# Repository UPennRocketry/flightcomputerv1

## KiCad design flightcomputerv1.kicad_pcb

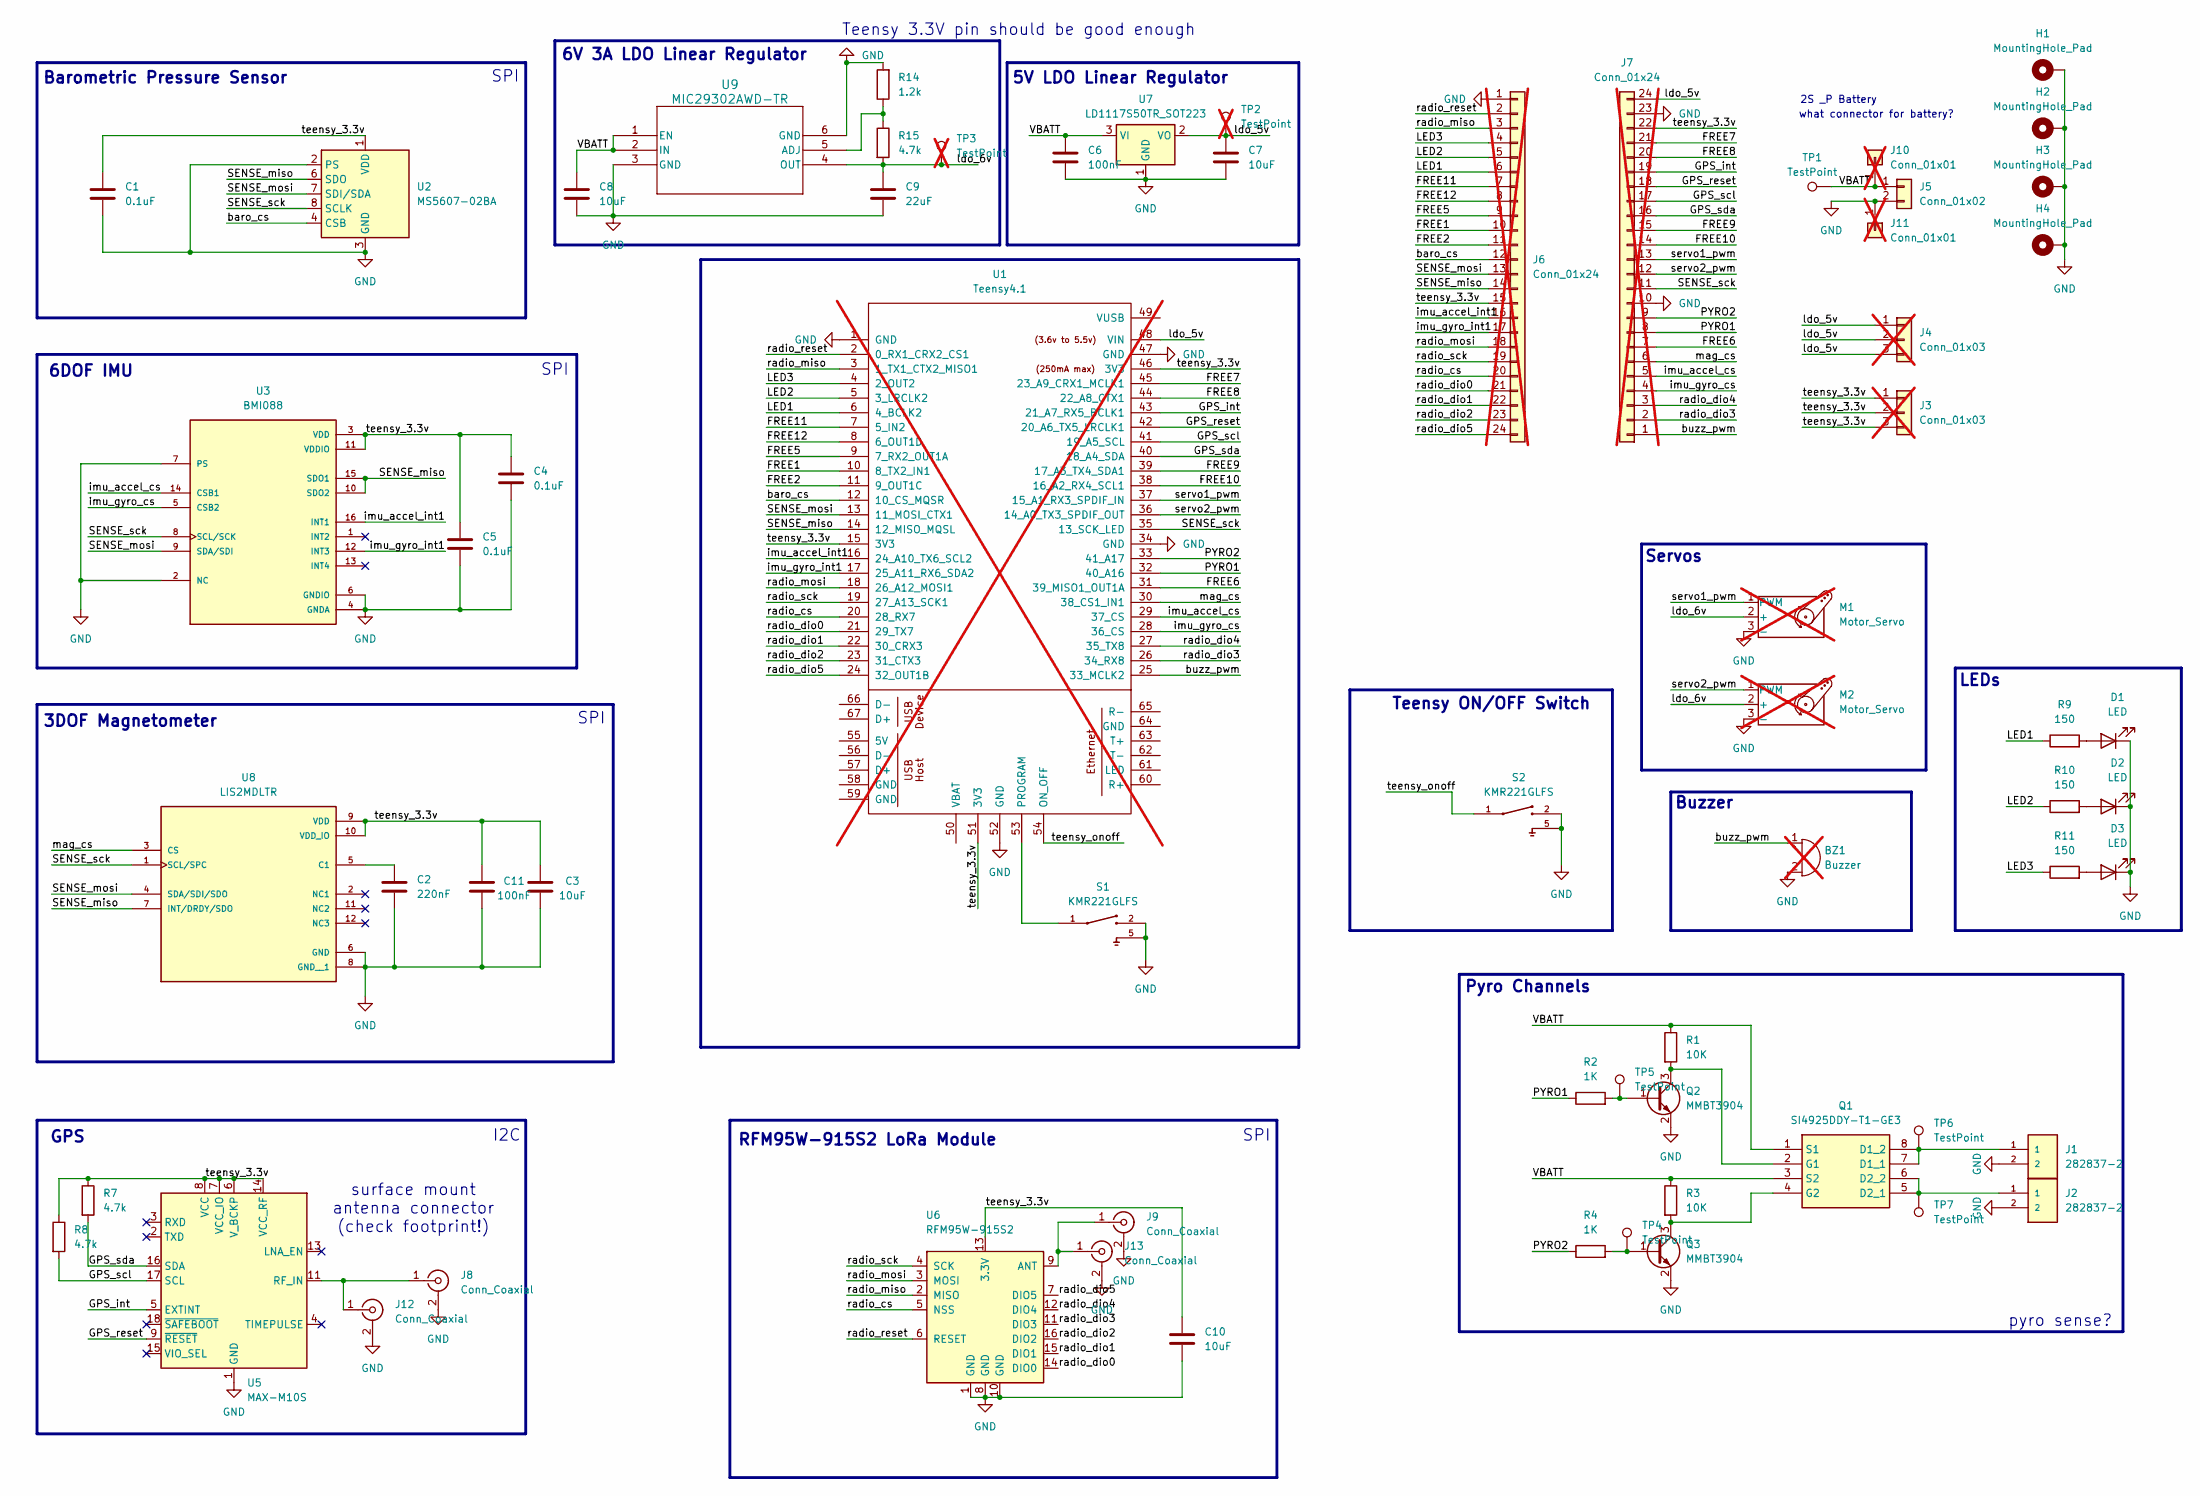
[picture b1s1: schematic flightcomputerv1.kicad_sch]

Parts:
BZ1: Buzzer; MagneticBuzzer_PUI_AT-0927-TT-6-R; MPN AT-0927-TT-6-R; not fitted
C1, C4, C5: 0.1uF; C_0402_1005Metric_Pad0.74x0.62mm_HandSolder
C2: 220nF; C_0402_1005Metric_Pad0.74x0.62mm_HandSolder
C3: 10uF; C_0402_1005Metric_Pad0.74x0.62mm_HandSolder
C6: 100nF; C_0603_1608Metric_Pad1.08x0.95mm_HandSolder
C7, C8, C10: 10uF; C_0603_1608Metric_Pad1.08x0.95mm_HandSolder
C9: 22uF; C_0603_1608Metric_Pad1.08x0.95mm_HandSolder
C11: 100nF; C_0402_1005Metric_Pad0.74x0.62mm_HandSolder
D1, D2, D3: LED; LED_0603_1608Metric_Pad1.05x0.95mm_HandSolder
H1, H2, H3, H4: MountingHole_Pad; MountingHole_2.2mm_M2_DIN965_Pad
J1, J2: 282837-2; TE_282837-2; PARTREV G3
J3, J4: Conn_01x03; PinHeader_1x03_P2.54mm_Vertical; not fitted
J5: Conn_01x02; JST_PH_S2B-PH-K_1x02_P2.00mm_Horizontal
J6, J7: Conn_01x24; Molex_SL_171971-0024_1x24_P2.54mm_Vertical; not fitted
J8, J9: Conn_Coaxial; SMA_Amphenol_132134-10_Vertical; MPN 132134
J10, J11: Conn_01x01; PinHeader_1x01_P2.54mm_Vertical; not fitted
J12, J13: Conn_Coaxial; U.FL_Hirose_U.FL-R-SMT-1_Vertical
M1, M2: Motor_Servo; PinHeader_1x03_P2.54mm_Vertical; not fitted
Q1: SI4925DDY-T1-GE3; SOIC127P600X175-8N; MPN SI4925DDY-T1-GE3
Q2: MMBT3904; SOT-23; MPN MMBT3904LT3G
Q3: MMBT3904; SOT-23
R1, R3: 10K; R_0603_1608Metric_Pad0.98x0.95mm_HandSolder
R2, R4: 1K; R_0603_1608Metric_Pad0.98x0.95mm_HandSolder
R7, R8, R15: 4.7k; R_0603_1608Metric_Pad0.98x0.95mm_HandSolder
R9, R10, R11: 150; R_0603_1608Metric_Pad0.98x0.95mm_HandSolder
R14: 1.2k; R_0603_1608Metric_Pad0.98x0.95mm_HandSolder
S1, S2: KMR221GLFS; SW_KMR221GLFS
TP1, TP4, TP5, TP6, TP7: TestPoint; TestPoint_Pad_1.0x1.0mm
TP2, TP3: TestPoint; PinHeader_1x01_P2.54mm_Vertical; not fitted
U1: Teensy4.1; Teensy41; not fitted
U2: MS5607-02BA; LGA-8_3x5mm_P1.25mm; MPN MS560702BA03-50
U3: BMI088; PQFN50P450X300X100-16N; MPN BMI088
U5: MAX-M10S; ublox_MAX; MPN MAX-M10S-00B
U6: RFM95W-915S2; HOPERF_RFM9XW_SMD; MPN RFM95W-915S2
U7: LD1117S50TR_SOT223; SOT-223-3_TabPin2; MPN LD1117S50TR
U8: LIS2MDLTR; PQFN50P200X200X70-12N; PARTREV Rev 5
U9: MIC29302AWD-TR; TO-252-5_MCH

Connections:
/FREE1: J6.10, U1.10 (8_TX2_IN1)
/FREE2: J6.11, U1.11 (9_OUT1C)
/FREE5: J6.9, U1.9 (7_RX2_OUT1A)
/FREE6: J7.7, U1.31 (39_MISO1_OUT1A)
/FREE7: J7.21, U1.45 (23_A9_CRX1_MCLK1)
/FREE8: J7.20, U1.44 (22_A8_CTX1)
/FREE9: J7.15, U1.39 (17_A3_TX4_SDA1)
/FREE10: J7.14, U1.38 (16_A2_RX4_SCL1)
/FREE11: J6.7, U1.7 (5_IN2)
/FREE12: J6.8, U1.8 (6_OUT1D)
/GPS_int: J7.19, U1.43 (21_A7_RX5_BCLK1), U5.5 (EXTINT)
/GPS_reset: J7.18, U1.42 (20_A6_TX5_LRCLK1), U5.9 (~RESET)
/GPS_scl: J7.17, R8.2, U1.41 (19_A5_SCL), U5.17 (SCL)
/GPS_sda: J7.16, R7.2, U1.40 (18_A4_SDA), U5.16 (SDA)
/LED1: J6.6, R9.1, U1.6 (4_BCLK2)
/LED2: J6.5, R10.1, U1.5 (3_LRCLK2)
/LED3: J6.4, R11.1, U1.4 (2_OUT2)
/PYRO1: J7.8, R2.1, U1.32 (40_A16)
/PYRO2: J7.9, R4.1, U1.33 (41_A17)
/SENSE_miso: J6.14, U1.14 (12_MISO_MQSL), U2.6 (SDO), U3.10 (SDO2), U3.15 (SDO1), U8.7 (INT/DRDY/SDO)
/SENSE_mosi: J6.13, U1.13 (11_MOSI_CTX1), U2.7 (SDI/SDA), U3.9 (SDA/SDI), U8.4 (SDA/SDI/SDO)
/SENSE_sck: J7.11, U1.35 (13_SCK_LED), U2.8 (SCLK), U3.8 (SCL/SCK), U8.1 (SCL/SPC)
/VBATT: C6.1, C8.1, J5.1, J10.1, Q1.1 (S1), Q1.3 (S2), R1.1, R3.1, TP1.1, U7.3 (VI), U9.1 (EN), U9.2 (IN)
/baro_cs: J6.12, U1.12 (10_CS_MQSR), U2.4 (CSB), U2.5 (CSB)
/buzz_pwm: BZ1.1 (+), J7.1, U1.25 (33_MCLK2)
/imu_accel_cs: J7.5, U1.29 (37_CS), U3.14 (CSB1)
/imu_accel_int1: J6.16, U1.16 (24_A10_TX6_SCL2), U3.16 (INT1)
/imu_gyro_cs: J7.4, U1.28 (36_CS), U3.5 (CSB2)
/imu_gyro_int1: J6.17, U1.17 (25_A11_RX6_SDA2), U3.12 (INT3)
/ldo_5v: C7.1, J4.1, J4.2, J4.3, J7.24, TP2.1, U1.48 (VIN), U7.2 (VO)
/ldo_6v: C9.1, M1.2 (+), M2.2 (+), R15.2, TP3.1, U9.4 (OUT)
/mag_cs: J7.6, U1.30 (38_CS1_IN1), U8.3 (CS)
/radio_cs: J6.20, U1.20 (28_RX7), U6.5 (NSS)
/radio_dio0: J6.21, U1.21 (29_TX7), U6.14 (DIO0)
/radio_dio1: J6.22, U1.22 (30_CRX3), U6.15 (DIO1)
/radio_dio2: J6.23, U1.23 (31_CTX3), U6.16 (DIO2)
/radio_dio3: J7.2, U1.26 (34_RX8), U6.11 (DIO3)
/radio_dio4: J7.3, U1.27 (35_TX8), U6.12 (DIO4)
/radio_dio5: J6.24, U1.24 (32_OUT1B), U6.7 (DIO5)
/radio_miso: J6.3, U1.3 (1_TX1_CTX2_MISO1), U6.2 (MISO)
/radio_mosi: J6.18, U1.18 (26_A12_MOSI1), U6.3 (MOSI)
/radio_reset: J6.2, U1.2 (0_RX1_CRX2_CS1), U6.6 (RESET)
/radio_sck: J6.19, U1.19 (27_A13_SCK1), U6.4 (SCK)
/servo1_pwm: J7.13, M1.1 (PWM), U1.37 (15_A1_RX3_SPDIF_IN)
/servo2_pwm: J7.12, M2.1 (PWM), U1.36 (14_A0_TX3_SPDIF_OUT)
/teensy_3.3v: C1.1, C3.1, C4.1, C5.1, C10.1, C11.1, J3.1, J3.2, J3.3, J6.15, J7.22, R7.1, R8.1, U1.15 (3V3), U1.46 (3V3), U1.51 (3V3), U2.1 (VDD), U3.3 (VDD), U3.11 (VDDIO), U5.6 (V_BCKP), U5.7 (VCC_IO), U5.8 (VCC), U5.14 (VCC_RF), U6.13 (3.3V), U8.9 (VDD), U8.10 (VDD_IO)
/teensy_onoff: S2.1, U1.54 (ON_OFF)
GND: BZ1.2 (-), C1.2, C2.2, C3.2, C4.2, C5.2, C6.2, C7.2, C8.2, C9.2, C10.2, C11.2, D1.1 (K), D2.1 (K), D3.1 (K), H1.1, H2.1, H3.1, H4.1, J1.2, J2.2, J5.2, J6.1, J7.10, J7.23, J8.2 (Ext), J9.2 (Ext), J11.1, J12.2 (Ext), J13.2 (Ext), M1.3 (-), M2.3 (-), Q2.2 (E), Q3.2 (E), R14.2, S1.2, S1.5, S2.2, S2.5, U1.1 (GND), U1.34 (GND), U1.47 (GND), U1.52 (GND), U2.2 (PS), U2.3 (GND), U3.2 (NC), U3.4 (GNDA), U3.6 (GNDIO), U3.7 (PS), U5.1 (GND), U5.10 (GND), U5.12 (GND), U6.1 (GND), U6.8 (GND), U6.10 (GND), U7.1 (GND), U8.6 (GND), U8.8 (GND__1), U9.3 (GND), U9.6 (GND)
unnamed: D1.2 (A), R9.2
unnamed: D2.2 (A), R10.2
unnamed: D3.2 (A), R11.2
unnamed: J8.1 (In), J12.1 (In), U5.11 (RF_IN)
unnamed: J9.1 (In), J13.1 (In), U6.9 (ANT)
unnamed: J1.1, Q1.7 (D1_1), Q1.8 (D1_2), TP6.1
unnamed: J2.1, Q1.5 (D2_1), Q1.6 (D2_2), TP7.1
unnamed: Q1.2 (G1), Q2.3 (C), R1.2
unnamed: Q1.4 (G2), Q3.3 (C), R3.2
unnamed: Q2.1 (B), R2.2, TP5.1
unnamed: Q3.1 (B), R4.2, TP4.1
unnamed: S1.1, U1.53 (PROGRAM)
unnamed: C2.1, U8.5 (C1)
unnamed: R14.1, R15.1, U9.5 (ADJ)

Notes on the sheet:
SPI
5V LDO Linear Regulator
LEDs
GPS
Barometric Pressure Sensor
surface mount antenna connector (check footprint!)
pyro sense?
2S _P Battery
Teensy 3.3V pin should be good enough
3DOF Magnetometer
6DOF IMU
Servos
Teensy ON/OFF Switch
Buzzer
RFM95W-915S2 LoRa Module
what connector for battery?
Pyro Channels
I2C
6V 3A LDO Linear Regulator

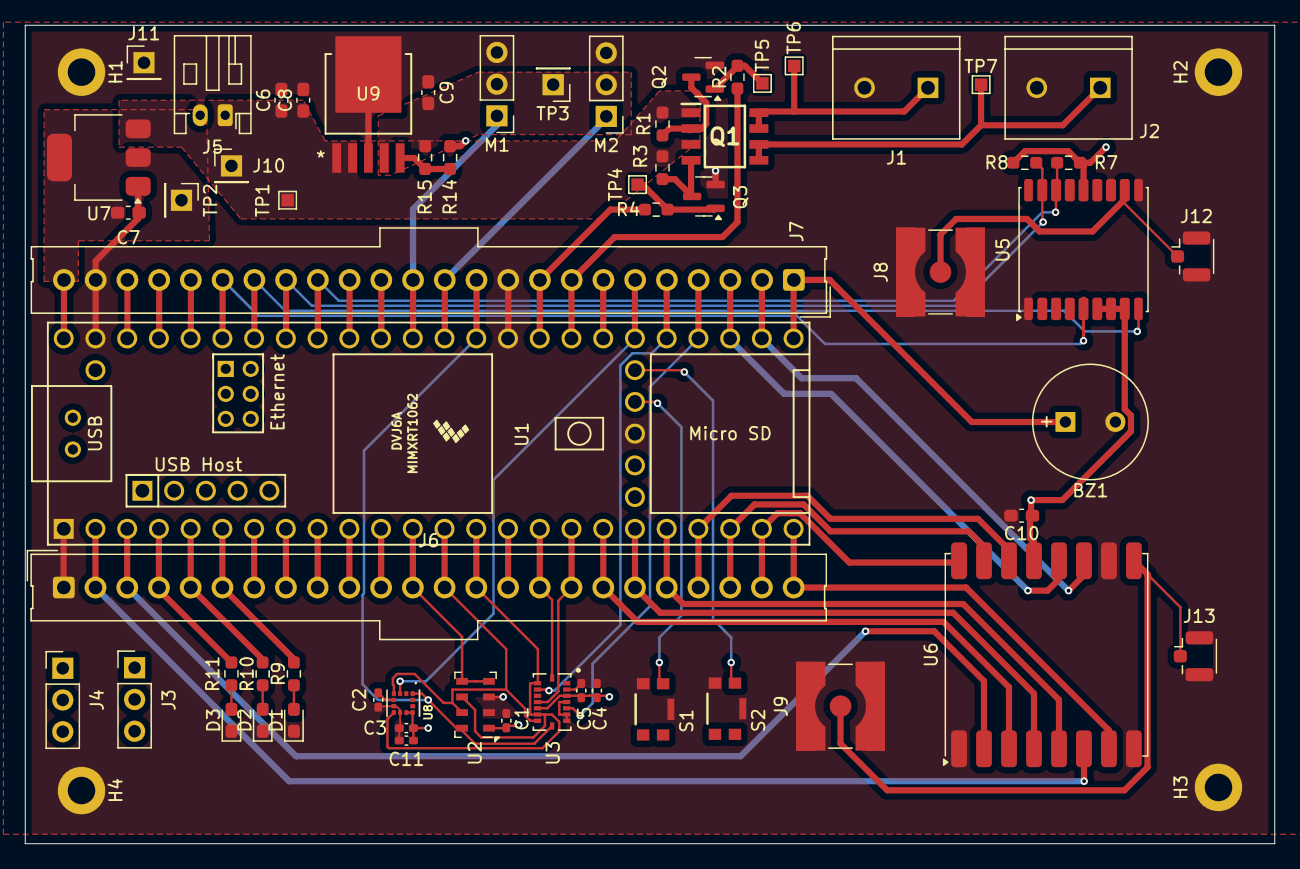
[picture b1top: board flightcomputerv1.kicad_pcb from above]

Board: 4 copper layers, 100.0 x 65.5 mm, 65 parts (0 on the bottom side), 62 nets.

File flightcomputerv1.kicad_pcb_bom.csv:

Designator,Quantity,Value,Footprint,Package,MPN,DNP,Mount_Type,Manufacturer,Description,Notes
BZ1,1,Buzzer,MagneticBuzzer_PUI_AT-0927-TT-6-R,THT,AT-0927-TT-6-R,,tht,PUI Audio,"Buzzer, polarized",
"C1, C4, C5",3,0.1uF,C_0201_0603Metric_Pad0.64x0.40mm_HandSolder,0603,,,smt,,"Unpolarized capacitor, 1% tolerance",generic
"C10, C3, C7, C8",4,10uF,C_0201_0603Metric_Pad0.64x0.40mm_HandSolder,0603,,,smt,,"Unpolarized capacitor, 1% tolerance",generic
C2,1,1uF,C_0201_0603Metric_Pad0.64x0.40mm_HandSolder,0603,,,smt,,"Unpolarized capacitor, 1% tolerance",generic
C6,1,100nF,C_0201_0603Metric_Pad0.64x0.40mm_HandSolder,0603,,,smt,,"Unpolarized capacitor, 1% tolerance",generic
C9,1,22uF,C_0201_0603Metric_Pad0.64x0.40mm_HandSolder,0603,,,smt,,"Unpolarized capacitor, 1% tolerance",generic
"D1, D2, D3",3,LED,LED_0402_1005Metric_Pad0.77x0.64mm_HandSolder,1005,,,smt,,Light emitting diode,generic
IC1,1,MMC5983MA,MMC5983MA_MEM,16-VFLGA,MMC5983MA,,smt,MEMSIC,3-AXIS MAGNETIC SENSOR,
"J1, J2",2,Screw_Terminal_01x02,TerminalBlock_TE_282834-2_1x02_P2.54mm_Horizontal,THT,282834-2,,tht,TE Connectivity AMP Connectors,TERM BLK 2P SIDE ENT 2.54MM PCB,Ensure screw terminals facing out of board
J10,1,Conn_01x01,PinHeader_1x01_P2.54mm_Vertical,THT,,Yes,tht,,"Generic connector, single row, 01x01, script generated (kicad-library-utils/schlib/autogen/connector/)",
J11,1,Conn_01x01,PinHeader_1x01_P2.54mm_Vertical,THT,,Yes,tht,,"Generic connector, single row, 01x01, script generated (kicad-library-utils/schlib/autogen/connector/)",
J3,1,Conn_01x03,PinHeader_1x03_P2.54mm_Vertical,THT,,Yes,tht,,"Generic connector, single row, 01x03, script generated (kicad-library-utils/schlib/autogen/connector/)",
J4,1,Conn_01x03,PinHeader_1x03_P2.54mm_Vertical,THT,,Yes,tht,,"Generic connector, single row, 01x03, script generated (kicad-library-utils/schlib/autogen/connector/)",
J5,1,Conn_01x02,JST_PH_S2B-PH-K_1x02_P2.00mm_Horizontal,THT,S2B-PH-K-S,,tht,JST Sales America Inc.,CONN HEADER R/A 2POS 2MM,
J6,1,Conn_01x24,Molex_SL_171971-0024_1x24_P2.54mm_Vertical,THT,,Yes,tht,,"Generic connector, single row, 01x24, script generated (kicad-library-utils/schlib/autogen/connector/)",
J7,1,Conn_01x24,Molex_SL_171971-0024_1x24_P2.54mm_Vertical,THT,,Yes,tht,,"Generic connector, single row, 01x24, script generated (kicad-library-utils/schlib/autogen/connector/)",
"J8, J9",2,Conn_Coaxial,SMA_Amphenol_132134-10_Vertical,SMD,132134,,smt,Amphenol RF,CONN SMA JACK STR 50 OHM PCB,
"M1, M2",2,Motor_Servo,PinHeader_1x03_P2.54mm_Vertical,THT,,,tht,,"Servo Motor (Futaba, HiTec, JR connector)",
Q1,1,SI4925DDY-T1-GE3,SOIC127P600X175-8N,"8-SOIC (0.154"", 3.90mm Width)",SI4925DDY-T1-GE3,,smt,Vishay Siliconix,"Vishay SI4925DDY-T1-GE3 Dual P-channel MOSFET Transistor, 8 A, 30 V, 8-Pin SOIC",
Q2,1,MMBT3904,SOT-23,SOT-23-3 (TO-236),MMBT3904LT3G,,smt,onsemi,"0.2A Ic, 40V Vce, Small Signal NPN Transistor, SOT-23",
Q3,1,MMBT3904,SOT-23,SOT-23-3 (TO-236),MMBT3904LT3G,,smt,onsemi,"0.2A Ic, 40V Vce, Small Signal NPN Transistor, SOT-23",
"R1, R3",2,10K,R_0201_0603Metric_Pad0.64x0.40mm_HandSolder,0603,,,smt,,"Resistor, 1% tolerance",generic
"R10, R11, R9",3,150,R_0201_0603Metric_Pad0.64x0.40mm_HandSolder,0603,,,smt,,"Resistor, 1% tolerance",generic
R14,1,1.2k,R_0201_0603Metric_Pad0.64x0.40mm_HandSolder,0603,,,smt,,"Resistor, 1% tolerance",generic
"R15, R7, R8",3,4.7k,R_0201_0603Metric_Pad0.64x0.40mm_HandSolder,0603,,,smt,,"Resistor, 1% tolerance",generic
"R2, R4",2,1K,R_0201_0603Metric_Pad0.64x0.40mm_HandSolder,0603,,,smt,,"Resistor, 1% tolerance",generic
S1,1,TS04-66-70-BK-160-SMT,SW_TS04-66-70-BK-160-SMT,Gull Wing,TS04-66-70-BK-160-SMT,,smt,Same Sky (Formerly CUI Devices),SWITCH TACTILE SPST-NO 0.05A 12V,generic
S2,1,TS04-66-70-BK-160-SMT,SW_TS04-66-70-BK-160-SMT,Gull Wing,TS04-66-70-BK-160-SMT,,smt,Same Sky (Formerly CUI Devices),SWITCH TACTILE SPST-NO 0.05A 12V,
"TP1, TP4, TP5, TP6, TP7",5,TestPoint,TestPoint_Pad_1.0x1.0mm,THT,,,tht,,test point,
"TP2, TP3",2,TestPoint,PinHeader_1x01_P2.54mm_Vertical,THT,,Yes,tht,,test point,
U1,1,Teensy4.1,Teensy41,,,Yes,tht,,,Will solder myself
U2,1,MS5607-02BA,LGA-8_3x5mm_P1.25mm,8-SMD,MS560702BA03-50,,smt,TE Connectivity Measurement Specialties,"Barometric pressure sensor, 20cm resolution, 10 to 1200 mbar, I2C and SPI interface up to 20MHz, LGA-8",
U3,1,BMI088,PQFN50P450X300X100-16N,16-VFLGA Module,BMI088,,smt,Bosch Sensortec,"Accelerometer, Gyroscope, 6 Axis Sensor I²C, SPI Output",
U4,1,MIC29302AWD,TO-252-5_TabPin3,"TO-252-6, DPAK (5 Leads + Tab)",MIC29302AWD-TR,,smt,Microchip Technology,"3A low dropout linear regulator, shutdown pin, 3V to 16V input voltage, 1.24V to 15V adjustable output, TO-252",
U5,1,MAX-M10S,ublox_MAX,18-SMD Module,MAX-M10S-00B,,smt,u-blox,"GNSS Module MAX M10, VCC 1.65V to 3.6V",
U6,1,RFM95W-915S2,HOPERF_RFM9XW_SMD,16-SMD Module,RFM95W-915S2,,smt,RF Solutions,"Low power long range transceiver module, SPI and parallel interface, 915 MHz, spreading factor 6 to12, bandwidth 7.8 to 500kHz, -111 to -148 dBm, SMD-16, DIP-16",
U7,1,LD1117S50TR_SOT223,SOT-223-3_TabPin2,"TO-261-4, TO-261AA",LD1117S50TR,,smt,STMicroelectronics,"800mA Fixed Low Drop Positive Voltage Regulator, Fixed Output 5.0V, SOT-223",

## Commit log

2024-12-10 first flight computer commit
2025-01-15 small update
2025-01-26 added radio module, still need footprint for either xbee or adafruit rfm95 breakout
2025-02-02 started placement
2025-02-07 started placement (repush)
2025-02-09 updated pcb + backups
2025-02-09 updated pcb
    routing more but they're kinda sus
2025-02-09 signal traces can via through the board
2025-02-16 updated placement and routing 2/16
2025-03-01 finished most of routing 2/28
2025-03-02 prelim routing placement done 3/2 need to check batt connector footprints + antenna connector + backup radio
2025-03-10 moved buttons
2025-03-11 magnetometer had wrong footprint. fixed all DRC errors. need to remake gerber
2025-03-20 still need to fill out BOM doc and get quote for assembly
2025-04-29 2025 FINAL
2025-09-28 final
2025-10-05 libs
